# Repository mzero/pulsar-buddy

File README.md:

# Pulsar Buddy

Pulsar Buddy is a small clock unit for the SOMA Lab's Pulsar-23 synth.
It is also useful with other modular synths.

Please see the [Wiki](https://github.com/mzero/pulsar-buddy/wiki) for full
information.

----

Pulsar Buddy is open source hardware and open source software.

The hardware is licensed by CC-SA-3.0. See LICENSE-HW.txt
The software is licensed by BSD3. See LICENSE-SW.txt

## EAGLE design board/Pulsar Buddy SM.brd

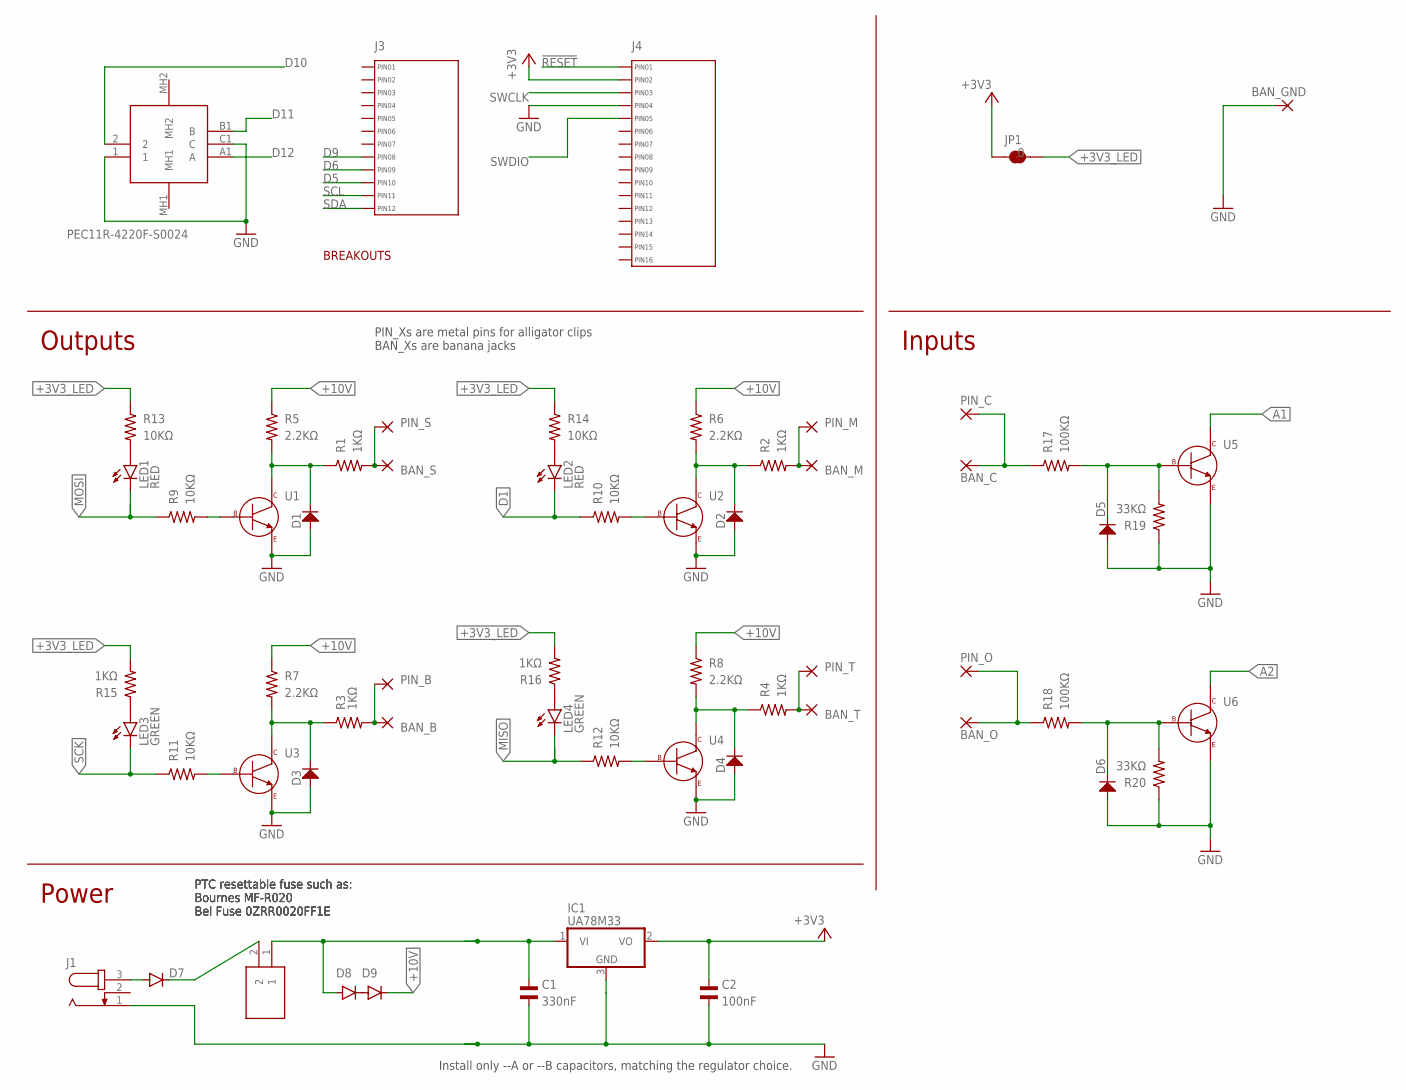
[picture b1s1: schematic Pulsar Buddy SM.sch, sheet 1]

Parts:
BAN_B: WIREPADBANANA; BANANA
BAN_C: WIREPADBANANA; BANANA
BAN_GND: WIREPADBANANA-GND; BANANA-GND
BAN_M: WIREPADBANANA; BANANA
BAN_O: WIREPADBANANA; BANANA
BAN_S: WIREPADBANANA; BANANA
BAN_T: WIREPADBANANA; BANANA
C1: 330nF; C0603; MPN CC0603ZRY5V7BB334
C2: 100nF; C0603; MPN CC0603KRX7R9BB104
D1, D2, D3, D4, D5, D6: MF-DIO-SOD123-BAT42; SOD-123
D7, D8, D9: CGRM4004-G; SOD-123_MINI-SMA; MPN CGRM4004-G
F1: 0ZCJ0020FF2E; FUSC3216X75N; MPN 0ZCJ0020FF2E
IC1: UA78M33; TO252; MPN UA78M33CKVURG3
J1: JACK-PLUG0; SPC4077
J3: MF-CON-2.54mm-01x12; PTH_2.54MM_01X12
J4: MF-CON-2.54mm-01x16; PTH_2.54MM_01X16
JP1: JUMPER-SMT_2_NC_TRACE_SILK; SMT-JUMPER_2_NC_TRACE_SILK
LED1, LED2: RED; LED5MM
LED3, LED4: GREEN; LED5MM
PIN_B: WIREPAD; M3
PIN_C: WIREPAD; M3
PIN_M: WIREPAD; M3
PIN_O: WIREPAD; M3
PIN_S: WIREPAD; M3
PIN_T: WIREPAD; M3
R1, R2, R3, R4, R15, R16: 1KΩ; R0603; MPN MF-RES-0603-1K
R5, R6, R7, R8: 2.2KΩ; R0603; MPN RC0603JR-072K2L
R9, R10, R11, R12, R13, R14: 10KΩ; R0603; MPN MF-RES-0603-10K
R17, R18: 100KΩ; R0603; MPN MF-RES-0603-100K
R19, R20: 33KΩ; R0603; MPN RC0603FR-0733KL
SW1: PEC11R-4220F-S0024; PEC11R4220FS0024; MPN PEC11R-4220F-S0024
U1, U2, U3, U4, U5, U6: MF-DSC-SOT233-MMBT3904; SOT-23-3

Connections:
!RESET: J4.P$1 (PIN1); also elsewhere on the board
+3V3: C2.P$1, IC1.2 (VO), J4.P$2 (PIN2), JP1.1; also elsewhere on the board
+3V3_LED: JP1.2, R13.P$1, R14.P$1, R15.P$2, R16.P$2
+10V: D9.C, R5.P$1, R6.P$1, R7.P$1, R8.P$1
+12V: C1.P$1, D8.A, F1.1, IC1.1 (VI)
A1: U5.P$3 (COLLECTOR); also elsewhere on the board
A2: U6.P$3 (COLLECTOR); also elsewhere on the board
D1: LED2.K (C), R10.P$1; also elsewhere on the board
D5: J3.P$10 (PIN10); also elsewhere on the board
D6: J3.P$9 (PIN9); also elsewhere on the board
D9: J3.P$8 (PIN8); also elsewhere on the board
D10: SW1.2; also elsewhere on the board
D11: SW1.B1 (B); also elsewhere on the board
D12: SW1.A1 (A); also elsewhere on the board
GND: BAN_GND.C, C1.P$2, C2.P$2, D1.ANODE, D2.ANODE, D3.ANODE, D4.ANODE, D5.ANODE, D6.ANODE, IC1.3 (GND), J1.1, J4.P$4 (PIN4), R19.P$1, R20.P$1, SW1.1, SW1.C1 (C), U1.P$2 (EMITTER), U2.P$2 (EMITTER), U3.P$2 (EMITTER), U4.P$2 (EMITTER), U5.P$2 (EMITTER), U6.P$2 (EMITTER); also elsewhere on the board
MISO: LED4.K (C), R12.P$1; also elsewhere on the board
MOSI: LED1.K (C), R9.P$1; also elsewhere on the board
unnamed: R10.P$2, U2.P$1 (BASE)
unnamed: D7.C, F1.2
unnamed: D7.A, J1.3
unnamed: LED1.A, R13.P$2
unnamed: LED2.A, R14.P$2
unnamed: R9.P$2, U1.P$1 (BASE)
unnamed: D1.CATHODE, R1.P$1, R5.P$2, U1.P$3 (COLLECTOR)
unnamed: D2.CATHODE, R2.P$1, R6.P$2, U2.P$3 (COLLECTOR)
unnamed: LED3.A, R15.P$1
unnamed: R11.P$2, U3.P$1 (BASE)
unnamed: D3.CATHODE, R3.P$1, R7.P$2, U3.P$3 (COLLECTOR)
unnamed: LED4.A, R16.P$1
unnamed: R12.P$2, U4.P$1 (BASE)
unnamed: D4.CATHODE, R4.P$1, R8.P$2, U4.P$3 (COLLECTOR)
unnamed: D5.CATHODE, R17.P$2, R19.P$2, U5.P$1 (BASE)
unnamed: BAN_O.C, PIN_O.1, R18.P$1
unnamed: BAN_C.C, PIN_C.1, R17.P$1
unnamed: D6.CATHODE, R18.P$2, R20.P$2, U6.P$1 (BASE)
unnamed: D8.C, D9.A
unnamed: BAN_S.C, PIN_S.1, R1.P$2
unnamed: BAN_M.C, PIN_M.1, R2.P$2
unnamed: BAN_T.C, PIN_T.1, R4.P$2
unnamed: BAN_B.C, PIN_B.1, R3.P$2
SCK: LED3.K (C), R11.P$1; also elsewhere on the board
SCL: J3.P$11 (PIN11); also elsewhere on the board
SDA: J3.P$12 (PIN12); also elsewhere on the board
SWCLK: J4.P$3 (PIN3); also elsewhere on the board
SWDIO: J4.P$5 (PIN5); also elsewhere on the board

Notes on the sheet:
Inputs
Power
Outputs
Install only --A or --B capacitors, matching the regulator choice.
PTC resettable fuse such as: Bournes MF-R020 Bel Fuse 0ZRR0020FF1E
BREAKOUTS
PIN_Xs are metal pins for alligator clips BAN_Xs are banana jacks

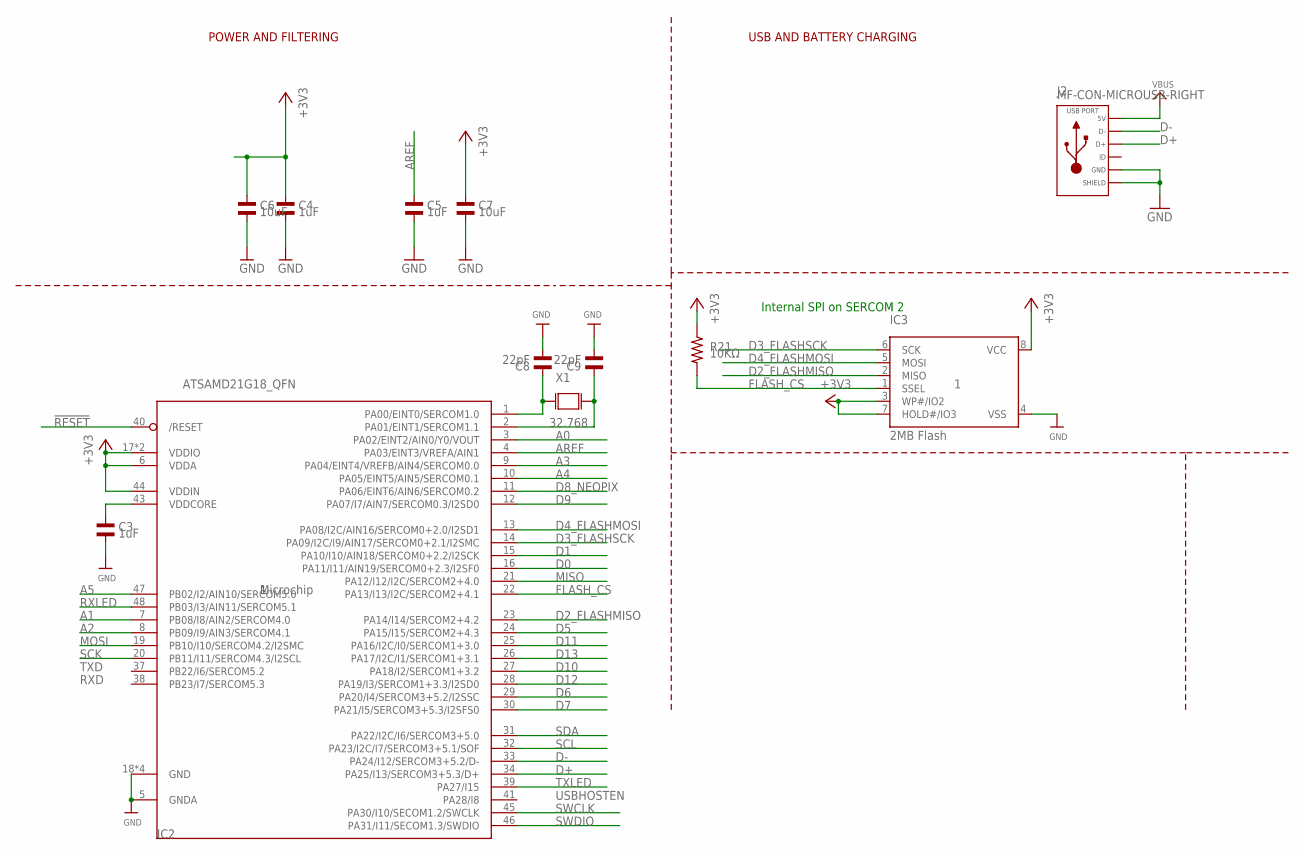
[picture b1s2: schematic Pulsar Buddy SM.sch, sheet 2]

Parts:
C3, C4, C5: 1uF; C0603; MPN MF-CAP-0603-1uF
C6, C7: 10uF; C0603; MPN 0603ZD106KAT2A
C8, C9: 22pF; C0603; MPN MF-CAP-0603-22pF
IC2: ATSAMD21G18_QFN; TQFN48_7MM; MPN SAMD21G18A-MU
IC3: 2MB Flash; SOIC8_208MIL; MPN S25FL064LABMFI010
J2: MF-CON-MICROUSB-RIGHT; MICROUSB-RIGHT
R21: 10KΩ; R0603; MPN MF-RES-0603-10K
U$34, U$35: FIDUCIAL_100MIL
X1: 32.768; ECX-31B_SERIES; MPN ECS-.327-7-12-C-TR

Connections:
!RESET: IC2.40 (/RESET); also elsewhere on the board
+3V3: C4.P$1, C6.P$1, C7.P$1, IC2.6 (VDDA), IC2.17 (VDDIO), IC2.36 (VDDIO), IC2.44 (VDDIN), IC3.3 (WP#/IO2), IC3.7 (HOLD#/IO3), IC3.8 (VCC), R21.P$1; also elsewhere on the board
A0: IC2.3 (PA02/EINT2/AIN0/Y0/VOUT)
A1: IC2.7 (PB08/I8/AIN2/SERCOM4.0); also elsewhere on the board
A2: IC2.8 (PB09/I9/AIN3/SERCOM4.1); also elsewhere on the board
A3: IC2.9 (PA04/EINT4/VREFB/AIN4/SERCOM0.0)
A4: IC2.10 (PA05/EINT5/AIN5/SERCOM0.1)
A5: IC2.47 (PB02/I2/AIN10/SERCOM5.0)
AREF: C5.P$1, IC2.4 (PA03/EINT3/VREFA/AIN1)
D0: IC2.16 (PA11/I11/AIN19/SERCOM0+2.3/I2SF0)
D1: IC2.15 (PA10/I10/AIN18/SERCOM0+2.2/I2SCK); also elsewhere on the board
D2_FLASHMISO: IC2.23 (PA14/I14/SERCOM2+4.2), IC3.2 (MISO)
D3_FLASHSCK: IC2.14 (PA09/I2C/I9/AIN17/SERCOM0+2.1/I2SMC), IC3.6 (SCK)
D4_FLASHMOSI: IC2.13 (PA08/I2C/AIN16/SERCOM0+2.0/I2SD1), IC3.5 (MOSI)
D5: IC2.24 (PA15/I15/SERCOM2+4.3); also elsewhere on the board
D6: IC2.29 (PA20/I4/SERCOM3+5.2/I2SSC); also elsewhere on the board
D7: IC2.30 (PA21/I5/SERCOM3+5.3/I2SFS0)
D8_NEOPIX: IC2.11 (PA06/EINT6/AIN6/SERCOM0.2)
D9: IC2.12 (PA07/I7/AIN7/SERCOM0.3/I2SD0); also elsewhere on the board
D10: IC2.27 (PA18/I2/SERCOM1+3.2); also elsewhere on the board
D11: IC2.25 (PA16/I2C/I0/SERCOM1+3.0); also elsewhere on the board
D12: IC2.28 (PA19/I3/SERCOM1+3.3/I2SD0); also elsewhere on the board
D13: IC2.26 (PA17/I2C/I1/SERCOM1+3.1)
D+: IC2.34 (PA25/I13/SERCOM3+5.3/D+), J2.3 (D+)
D-: IC2.33 (PA24/I12/SERCOM3+5.2/D-), J2.2 (D-)
FLASH_CS: IC2.22 (PA13/I13/I2C/SERCOM2+4.1), IC3.1 (SSEL), R21.P$2
GND: C3.P$2, C4.P$2, C5.P$2, C6.P$2, C7.P$2, C8.P$2, C9.P$2, IC2.5 (GNDA), IC2.18 (GND), IC2.35 (GND), IC2.42 (GND), IC2.THERMAL (GND), IC3.4 (VSS), J2.5 (GND), J2.S1 (SLD), J2.S2 (SLD), J2.S3 (SLD), J2.S4 (SLD), J2.S5 (SLD), J2.S6 (SLD); also elsewhere on the board
MISO: IC2.21 (PA12/I12/I2C/SERCOM2+4.0); also elsewhere on the board
MOSI: IC2.19 (PB10/I10/SERCOM4.2/I2SMC); also elsewhere on the board
unnamed: C8.P$1, IC2.1 (PA00/EINT0/SERCOM1.0), X1.P$1 (X0)
unnamed: C9.P$1, IC2.2 (PA01/EINT1/SERCOM1.1), X1.P$2 (X1)
RXLED: IC2.48 (PB03/I3/AIN11/SERCOM5.1)
SCK: IC2.20 (PB11/I11/SERCOM4.3/I2SCL); also elsewhere on the board
SCL: IC2.32 (PA23/I2C/I7/SERCOM3+5.1/SOF); also elsewhere on the board
SDA: IC2.31 (PA22/I2C/I6/SERCOM3+5.0); also elsewhere on the board
SWCLK: IC2.45 (PA30/I10/SECOM1.2/SWCLK); also elsewhere on the board
SWDIO: IC2.46 (PA31/I11/SECOM1.3/SWDIO); also elsewhere on the board
TXLED: IC2.39 (PA27/I15)
VBUS: J2.1 (5V)
VDDCORE1: C3.P$1, IC2.43 (VDDCORE)

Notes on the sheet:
POWER AND FILTERING
USBHOSTEN
TXD
RXD
USB AND BATTERY CHARGING
Internal SPI on SERCOM 2

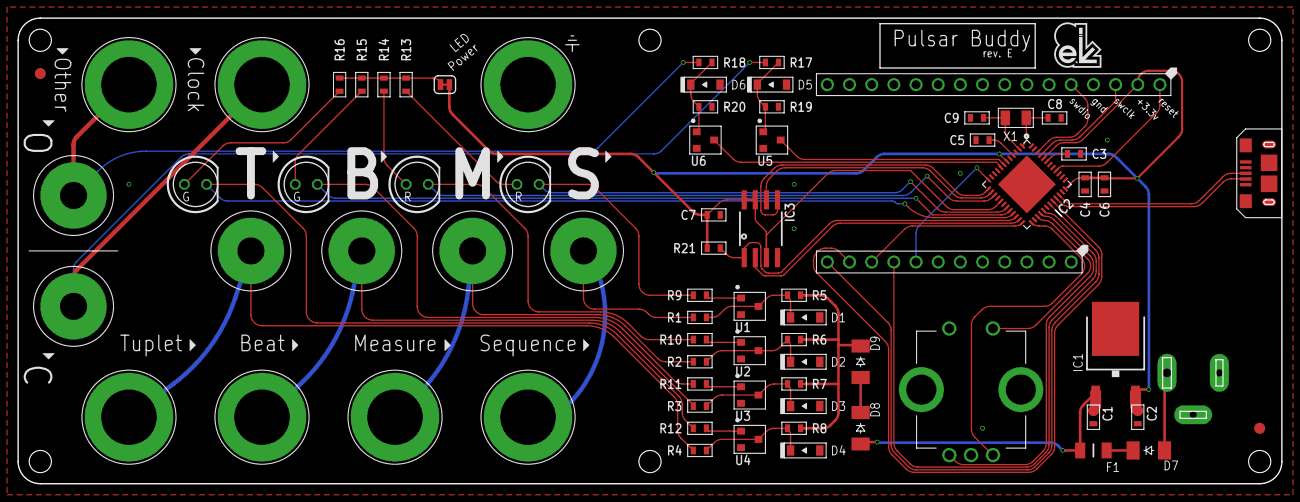
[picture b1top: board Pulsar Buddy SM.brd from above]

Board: 2 copper layers, 144.8 x 53.3 mm, 75 parts (1 on the bottom side), 55 nets.

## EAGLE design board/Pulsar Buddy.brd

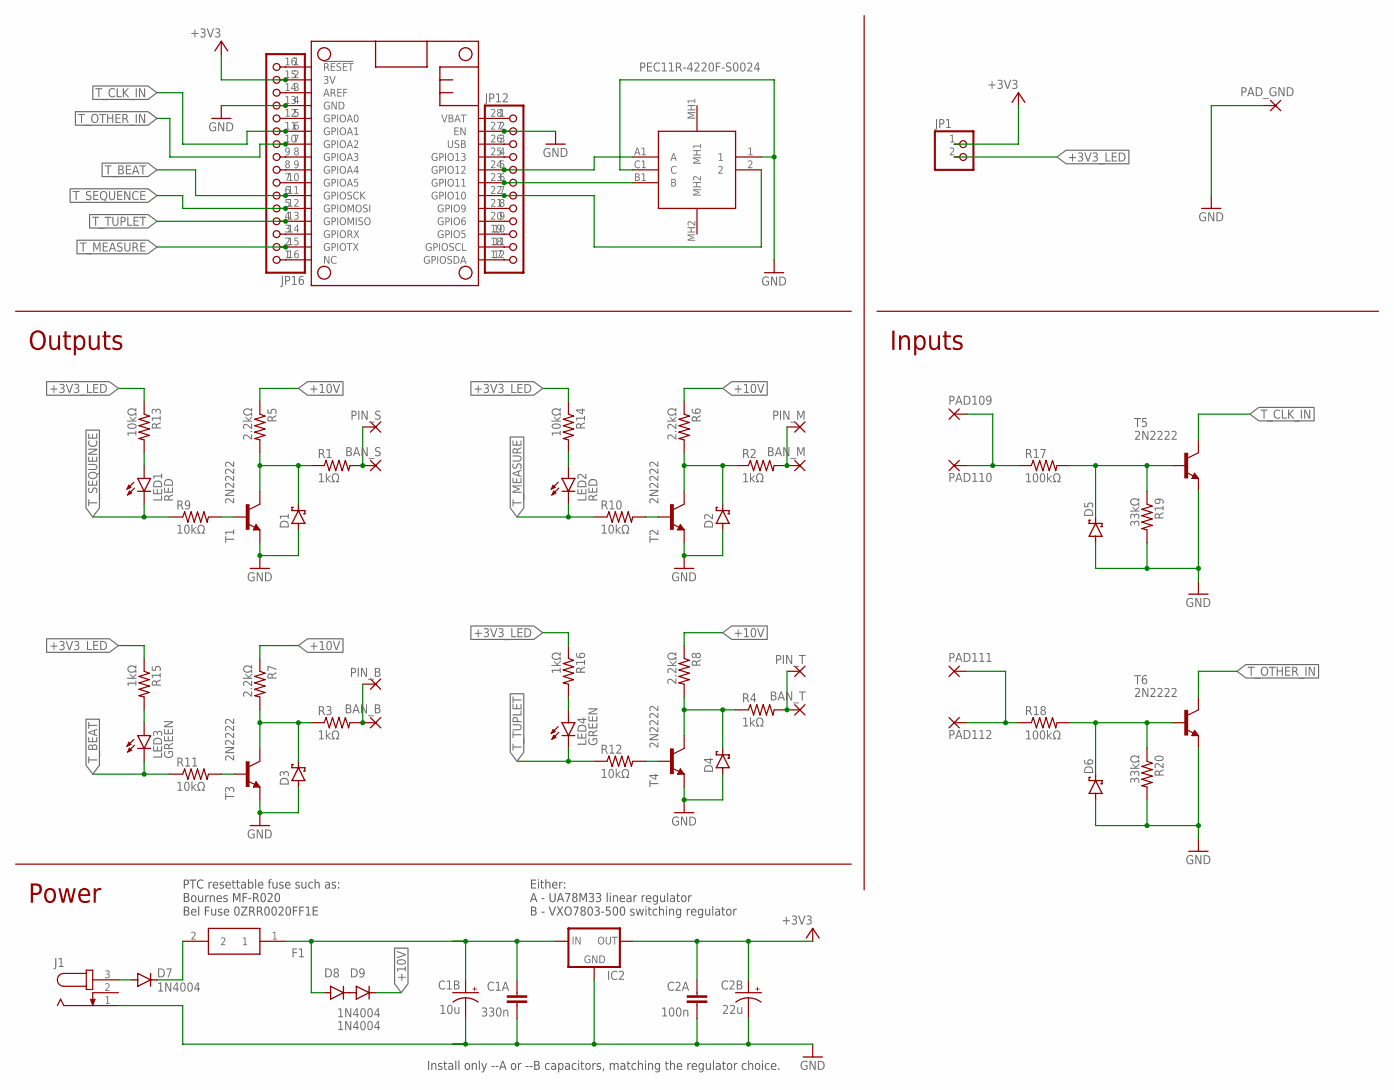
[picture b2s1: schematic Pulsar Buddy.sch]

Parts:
BAN_B: WIREPADBANANA; BANANA
BAN_M: WIREPADBANANA; BANANA
BAN_S: WIREPADBANANA; BANANA
BAN_T: WIREPADBANANA; BANANA
C1A: 330n; C025-024X044
C1B: 10u; E5-5
C2A: 100n; C025-024X044
C2B: 22u; E5-5
D1, D2, D3, D4, D5, D6: SCHOTTKY-DIODEDO35-7; DO35-7
D7, D8, D9: 1N4004; DO41-10
F1: 0ZRR0025FF1E
IC2: UA78M33CKCSTO-220; TO220H
J1: JACK-PLUG0; SPC4077
JP1: PINHD-1X2; 1X02
JP12: HEADER-1X12; 1X12_ROUND
JP16: HEADER-1X16ROUND; 1X16_ROUND
LED1, LED2: RED; LED5MM
LED3, LED4: GREEN; LED5MM
MS101: FEATHERWING_NODIM; FEATHERWING_DIM
PAD109, PAD111: WIREPAD; M3
PAD110, PAD112: WIREPADBANANA; BANANA
PAD_GND: WIREPADBANANA-GND; BANANA-GND
PIN_B: WIREPAD; M3
PIN_M: WIREPAD; M3
PIN_S: WIREPAD; M3
PIN_T: WIREPAD; M3
R1, R2, R3, R4, R15, R16: 1kΩ; 0204/7
R5, R6, R7, R8: 2.2kΩ; 0204/7
R9, R10, R11, R12, R13, R14: 10kΩ; 0204/7
R17, R18: 100kΩ; 0204/7
R19, R20: 33kΩ; 0204/7
SW1: PEC11R-4220F-S0024; PEC11R4220FS0024
T1, T2, T3, T4, T5, T6: 2N2222; TO92-EBC-OVAL

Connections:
+3V3: C2A.1, C2B.+, IC2.3 (OUT), JP1.1, JP16.15, MS101.2 (3V)
+3V3_LED: JP1.2, R13.1, R14.1, R15.1, R16.1
+5V_CPU: JP12.3, MS101.26 (USB)
+10V: D9.C, R5.1, R6.1, R7.1, R8.1
+12V: C1A.1, C1B.+, D8.A, F1.1, IC2.1 (IN)
GND: C1A.2, C1B.-, C2A.2, C2B.-, D1.A, D2.A, D3.A, D4.A, D5.A, D6.A, IC2.2 (GND), J1.1, JP12.2, JP16.13, MS101.4 (GND), MS101.27 (EN), PAD_GND.C, R19.2, R20.2, SW1.1, SW1.C1 (C), T1.E, T2.E, T3.E, T4.E, T5.E, T6.E
unnamed: JP12.5, MS101.24 (GPIO12), SW1.A1 (A)
unnamed: JP12.7, MS101.22 (GPIO10), SW1.2
unnamed: JP12.6, MS101.23 (GPIO11), SW1.B1 (B)
unnamed: D7.C, F1.2
unnamed: D7.A, J1.3
unnamed: LED1.A, R13.2
unnamed: LED2.A, R14.2
unnamed: R9.2, T1.B
unnamed: D1.C, R1.1, R5.2, T1.C
unnamed: R10.2, T2.B
unnamed: D2.C, R2.1, R6.2, T2.C
unnamed: LED3.A, R15.2
unnamed: R11.2, T3.B
unnamed: D3.C, R3.1, R7.2, T3.C
unnamed: LED4.A, R16.2
unnamed: R12.2, T4.B
unnamed: D4.C, R4.1, R8.2, T4.C
unnamed: D5.C, R17.2, R19.1, T5.B
unnamed: PAD111.1, PAD112.C, R18.1
unnamed: PAD109.1, PAD110.C, R17.1
unnamed: D6.C, R18.2, R20.1, T6.B
unnamed: JP16.16, MS101.1 (!RESET)
unnamed: JP16.14, MS101.3 (AREF)
unnamed: JP16.12, MS101.5 (GPIOA0)
unnamed: JP16.9, MS101.8 (GPIOA3)
unnamed: JP16.8, MS101.9 (GPIOA4)
unnamed: JP16.7, MS101.10 (GPIOA5)
unnamed: JP16.3, MS101.14 (GPIORX)
unnamed: JP16.1, MS101.16 (NC)
unnamed: JP12.12, MS101.17 (GPIOSDA)
unnamed: JP12.11, MS101.18 (GPIOSCL)
unnamed: JP12.10, MS101.19 (GPIO5)
unnamed: JP12.8, MS101.21 (GPIO9)
unnamed: JP12.9, MS101.20 (GPIO6)
unnamed: JP12.4, MS101.25 (GPIO13)
unnamed: D8.C, D9.A
unnamed: BAN_S.C, PIN_S.1, R1.2
unnamed: BAN_M.C, PIN_M.1, R2.2
unnamed: BAN_T.C, PIN_T.1, R4.2
unnamed: BAN_B.C, PIN_B.1, R3.2
T_BEAT: JP16.6, LED3.K (C), MS101.11 (GPIOSCK), R11.1
T_CLK_IN: JP16.11, MS101.6 (GPIOA1), T5.C
T_MEASURE: JP16.2, LED2.K (C), MS101.15 (GPIOTX), R10.1
T_OTHER_IN: JP16.10, MS101.7 (GPIOA2), T6.C
T_SEQUENCE: JP16.5, LED1.K (C), MS101.12 (GPIOMOSI), R9.1
T_TUPLET: JP16.4, LED4.K (C), MS101.13 (GPIOMISO), R12.1
VBAT: JP12.1, MS101.28 (VBAT)

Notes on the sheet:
Inputs
Power
Outputs
Either: A - UA78M33 linear regulator B - VXO7803-500 switching regulator
Install only --A or --B capacitors, matching the regulator choice.
PTC resettable fuse such as: Bournes MF-R020 Bel Fuse 0ZRR0020FF1E

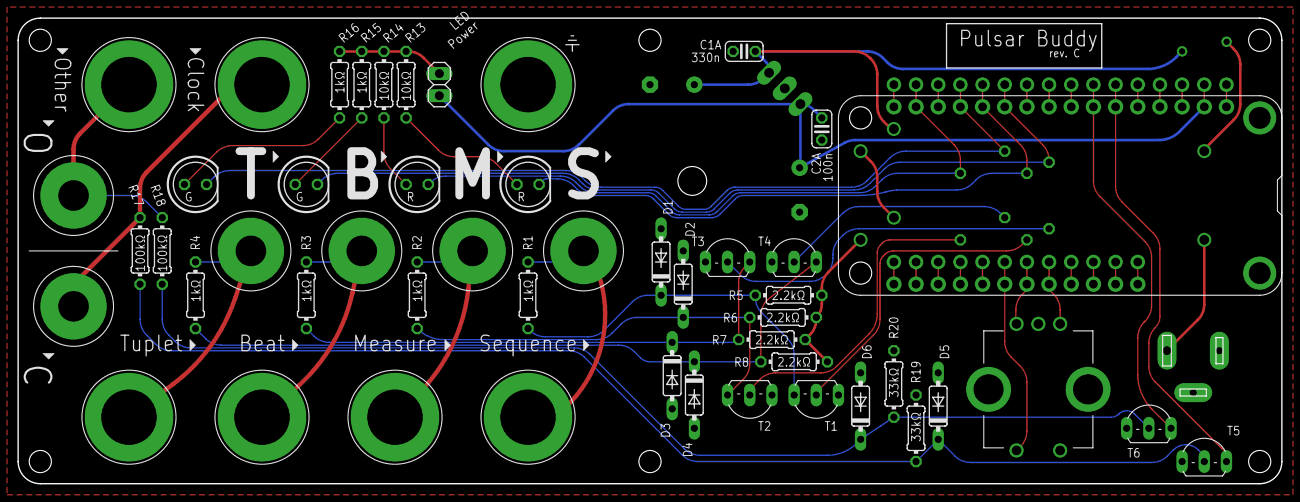
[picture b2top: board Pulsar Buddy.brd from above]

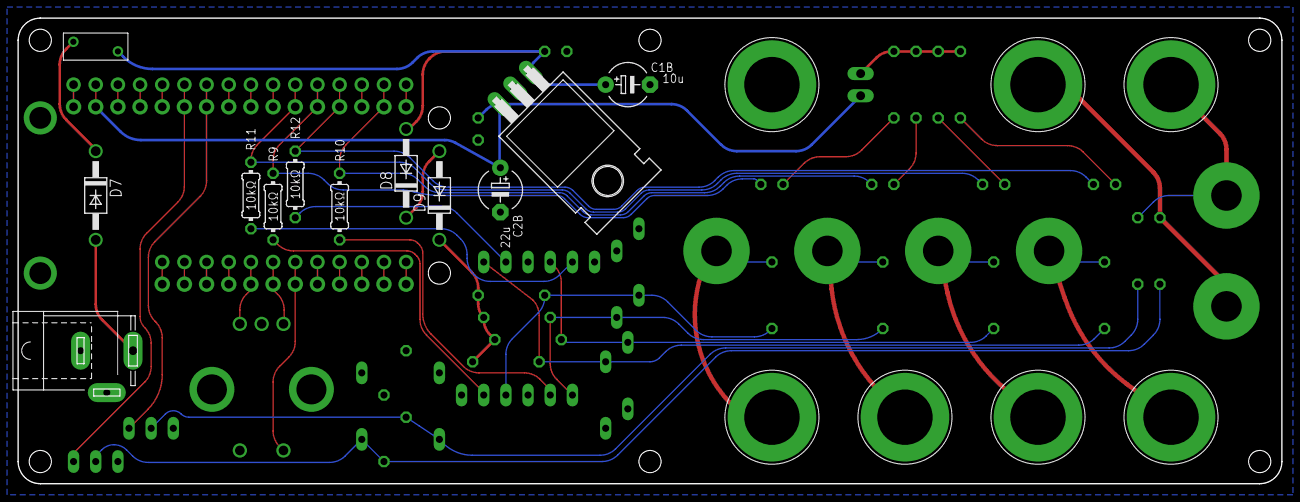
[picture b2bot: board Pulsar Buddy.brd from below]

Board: 2 copper layers, 144.8 x 53.3 mm, 64 parts (12 on the bottom side), 53 nets.

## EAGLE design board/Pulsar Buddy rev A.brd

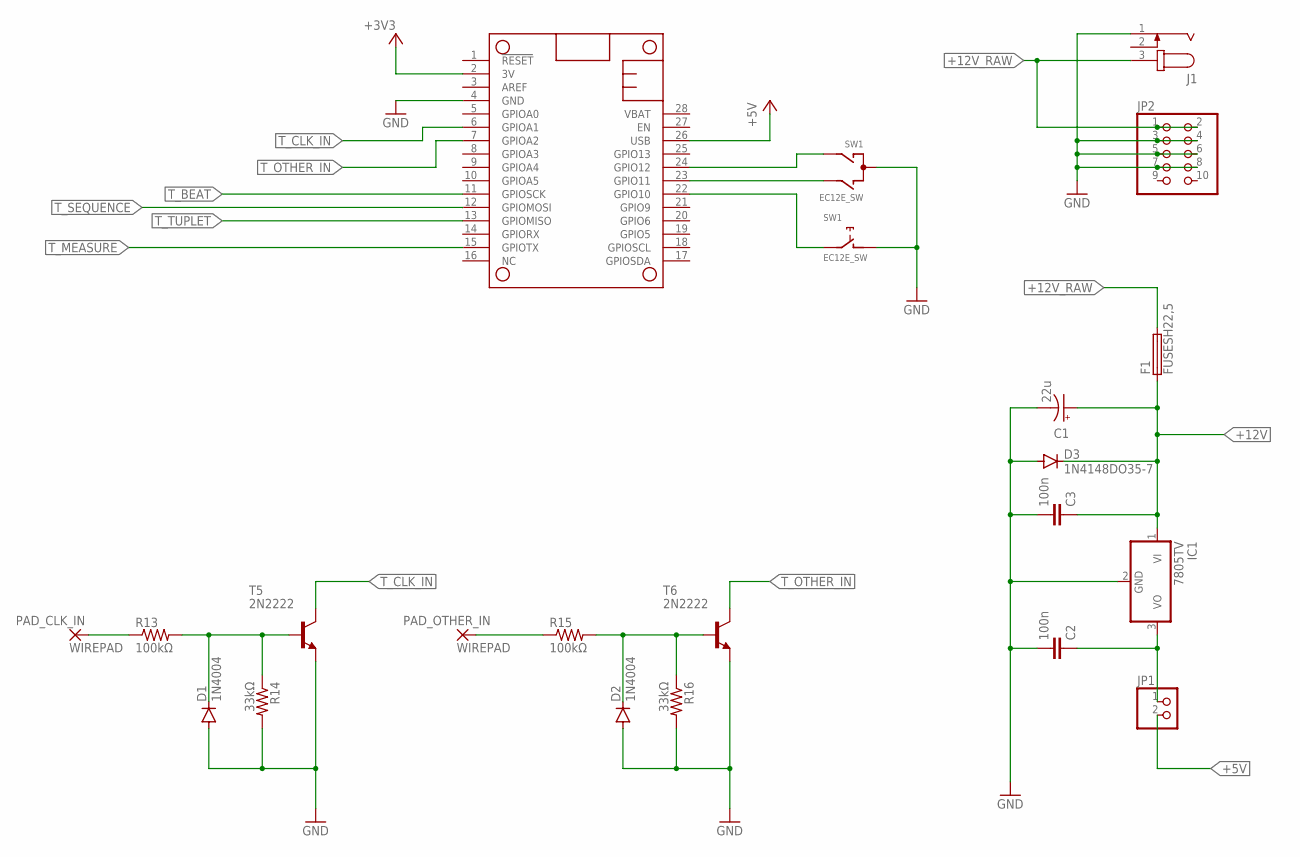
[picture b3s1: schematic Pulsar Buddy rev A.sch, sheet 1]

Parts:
C1: 22u; E3,5-8
C2, C3: 100n; C025-024X044
D1, D2: 1N4004; DO41-10
D3: 1N4148DO35-7; DO35-7
F1: FUSESH22,5; SH22,5
IC1: 7805TV; TO220V
J1: JACK-PLUG0; SPC4077
JP1: PINHD-1X2; 1X02
JP2: PINHD-2X5; 2X05
MS2: FEATHERWING_NODIM; FEATHERWING_DIM
PAD_CLK_IN: WIREPAD; M3
PAD_OTHER_IN: WIREPAD; M3
R13, R15: 100kΩ; 0204/7
R14, R16: 33kΩ; 0204/7
SW1: EC12E_SW; ALPS_EC12E_SW
T5, T6: 2N2222; TO92-EBC-OVAL

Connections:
+3V3: MS2.2 (3V); also elsewhere on the board
+5V: JP1.2, MS2.26 (USB); also elsewhere on the board
+12V: C1.+, C3.1, D3.C, F1.1, IC1.1 (VI); also elsewhere on the board
+12V_RAW: F1.2, J1.3, JP2.1, JP2.2
GND: C1.-, C2.2, C3.2, D1.A, D2.A, D3.A, IC1.2 (GND), J1.1, JP2.3, JP2.4, JP2.5, JP2.6, JP2.7, JP2.8, MS2.4 (GND), R14.2, R16.2, SW1.C, SW1.D (1), T5.E, T6.E; also elsewhere on the board
unnamed: MS2.24 (GPIO12), SW1.A
unnamed: MS2.22 (GPIO10), SW1.E (2)
unnamed: MS2.23 (GPIO11), SW1.B
unnamed: C2.1, IC1.3 (VO), JP1.1
unnamed: D1.C, R13.2, R14.1, T5.B
unnamed: PAD_OTHER_IN.1, R15.1
unnamed: PAD_CLK_IN.1, R13.1
unnamed: D2.C, R15.2, R16.1, T6.B
T_BEAT: MS2.11 (GPIOSCK); also elsewhere on the board
T_CLK_IN: MS2.6 (GPIOA1), T5.C
T_MEASURE: MS2.15 (GPIOTX); also elsewhere on the board
T_OTHER_IN: MS2.7 (GPIOA2), T6.C
T_SEQUENCE: MS2.12 (GPIOMOSI); also elsewhere on the board
T_TUPLET: MS2.13 (GPIOMISO); also elsewhere on the board

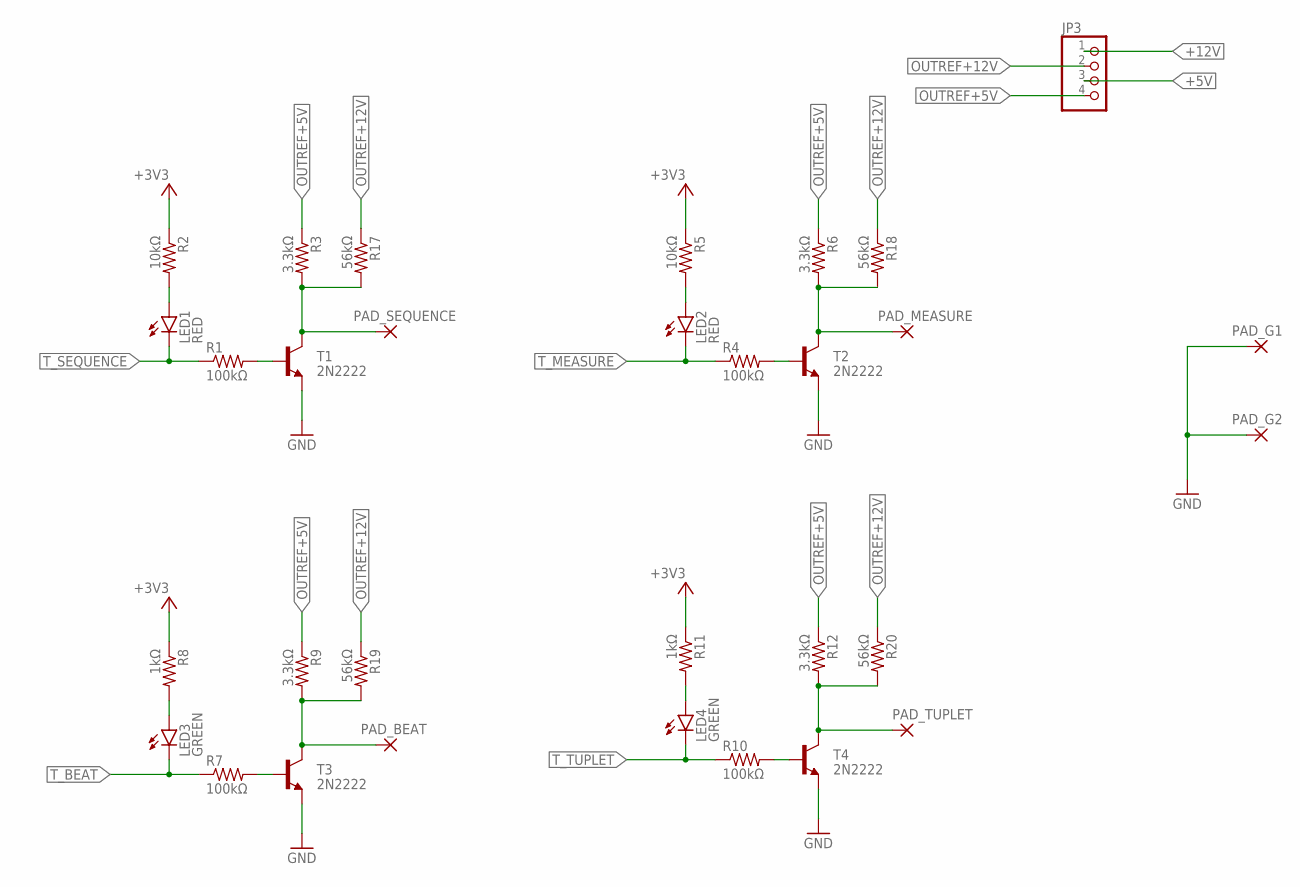
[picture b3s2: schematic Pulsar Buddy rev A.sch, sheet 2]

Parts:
JP3: PINHD-1X4; 1X04
LED1, LED2: RED; LED5MM
LED3, LED4: GREEN; LED5MM
PAD_BEAT: WIREPAD; M3
PAD_G1, PAD_G2: WIREPAD; M3
PAD_MEASURE: WIREPAD; M3
PAD_SEQUENCE: WIREPAD; M3
PAD_TUPLET: WIREPAD; M3
R1, R4, R7, R10: 100kΩ; 0204/7
R2, R5: 10kΩ; 0204/7
R3, R6, R9, R12: 3.3kΩ; 0204/7
R8, R11: 1kΩ; 0204/7
R17, R18, R19, R20: 56kΩ; 0204/7
T1, T2, T3, T4: 2N2222; TO92-EBC-OVAL

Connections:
+3V3: R2.1, R5.1, R8.1, R11.1; also elsewhere on the board
+5V: JP3.3; also elsewhere on the board
+12V: JP3.1; also elsewhere on the board
GND: PAD_G1.1, PAD_G2.1, T1.E, T2.E, T3.E, T4.E; also elsewhere on the board
unnamed: LED1.A, R2.2
unnamed: LED2.A, R5.2
unnamed: R1.2, T1.B
unnamed: PAD_SEQUENCE.1, R3.2, R17.2, T1.C
unnamed: R4.2, T2.B
unnamed: PAD_MEASURE.1, R6.2, R18.2, T2.C
unnamed: LED3.A, R8.2
unnamed: R7.2, T3.B
unnamed: PAD_BEAT.1, R9.2, R19.2, T3.C
unnamed: LED4.A, R11.2
unnamed: R10.2, T4.B
unnamed: PAD_TUPLET.1, R12.2, R20.2, T4.C
OUTREF+5V: JP3.4, R3.1, R6.1, R9.1, R12.1
OUTREF+12V: JP3.2, R17.1, R18.1, R19.1, R20.1
T_BEAT: LED3.K (C), R7.1; also elsewhere on the board
T_MEASURE: LED2.K (C), R4.1; also elsewhere on the board
T_SEQUENCE: LED1.K (C), R1.1; also elsewhere on the board
T_TUPLET: LED4.K (C), R10.1; also elsewhere on the board

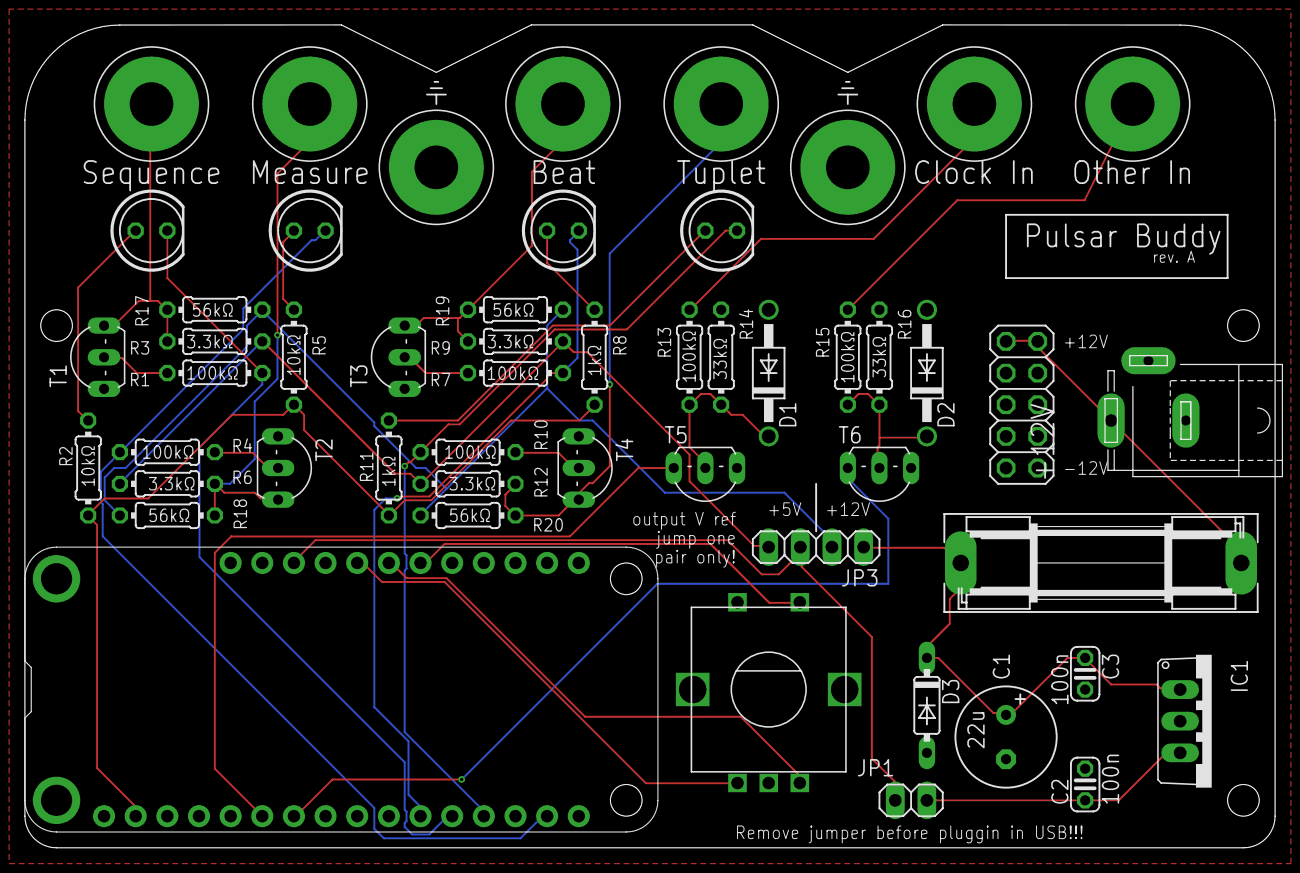
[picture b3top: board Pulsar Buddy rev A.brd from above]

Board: 2 copper layers, 100.3 x 66.0 mm, 52 parts (0 on the bottom side), 33 nets.

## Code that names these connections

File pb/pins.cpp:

#include "pins.h"

#include <Arduino.h>
#include <wiring_private.h>

/*
  Output pins are:
                timer   wave    samd pin    arduino pin
    SEQUENCE:   TCC0    WO4     PB10        29, PIN_SPI_MOSI
    MEASURE:    TCC1    WO0     PA10         1, PIN_SERIAL1_TX
    BEAT:       TC5     WO1     PB11        30, PIN_SPI_SCK
    TUPLET:     TCC2    WO0     PA12        28, PIN_SPI_MISO

    Despite the Adafruit's pinout diagram, these are the actual library pin
    numbers for the SPI pins on the Feather M0 Express.

  Input pins:
    EXT CLK:                    PB08        15, PIN_A1
    OTHER:                      PB09        16, PIN_A2


  NB: If you want to change the pin assignments, then you must carefully
  review and adjust the timer assignments in timer_hw.cpp so that each
  timer has an output waveform that can be assigned to the pin you want to
  use.

*/

TriggerOutput TriggerOutput::S(PIN_SPI_MOSI);
TriggerOutput TriggerOutput::M(PIN_SERIAL1_TX);
TriggerOutput TriggerOutput::B(PIN_SPI_SCK);
TriggerOutput TriggerOutput::T(PIN_SPI_MISO);

TriggerInput TriggerInput::C(PIN_A1);
TriggerInput TriggerInput::O(PIN_A2);


// NORMAL OPERATION

void TriggerOutput::initialize() {
  // Pins are configured as outputs, first, set to HIGH...
  // ...then configured to output the from the peripheral multiplexor.
  // This way, all triggers can be forced off (HIGH, they invert), by just
  // disabling the multiplexor for them.

  digitalWrite(pin, HIGH);
  pinPeripheral(pin, pin == PIN_SPI_MOSI ? PIO_TIMER_ALT : PIO_TIMER);
}

void TriggerOutput::disable(bool off) {
  PORT->Group[g_APinDescription[pin].ulPort]
    .PINCFG[g_APinDescription[pin].ulPin]
      .bit.PMUXEN = off ? 0 : 1;
}

void TriggerInput::initialize() {
  pinMode(pin, INPUT_PULLUP);
  pinPeripheral(pin, PIO_EXTINT);
}

bool TriggerInput::read() {
  return digitalRead(pin) == LOW;     // inputs are inverted
}


// TEST MODE OPERATION

void TriggerOutput::testInitialize() {
  pinMode(pin, OUTPUT);
  pinPeripheral(pin, PIO_OUTPUT);
}

void TriggerOutput::testWrite(bool on) {
  digitalWrite(pin, on ? LOW : HIGH);   // outputs are inverted
}


void TriggerInput::testInitialize() {
  pinMode(pin, INPUT_PULLUP);
  pinPeripheral(pin, PIO_INPUT_PULLUP);
}

bool TriggerInput::testRead() {
  return digitalRead(pin) == LOW;     // inputs are inverted
}

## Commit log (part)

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2019-11-23 first sketch w/working UI
2019-11-23 work on display routines
2019-11-24 Field and ValueField templates & selection menus
2019-11-24 dim timer
    - and some Serial debugging cleanups
2019-11-24 sublime project
2019-11-24 include separators in compound option fields
2019-11-25 make list of fields be a std::initializer_list
2019-11-25 some small C++ cleanups
2019-11-26 quantum and beat timers!!
2019-11-26 breaking out timing.h/.cpp
2019-11-27 make beat output be the beat from the tuplet
2019-11-27 remove unneeded pinMode() calls
2019-11-30 circuit and layout files
2019-11-30 update to TODO
2019-11-30 simplify memory display
2019-11-30 plumb interrupt to main loop on each measure
2019-11-30 state improvements
    - Settings and State classes
    - user and active Settings
    - commit to active settings on measure events
2019-12-01 button states
2019-12-01 plumb encoder button state to Filed::click() in case the selected field wants it
2019-12-01 complete memory UI
    - selection and update updates a temporary selection
    - click loads selection
    - long press saves into selected memory - with UI feedback
2019-12-01 added enter() and exit() functions for Fields
2019-12-01 support for preview state
2019-12-02 first flash storage
2019-12-03 flash improvements: new hash, and speed up bitmap scan loop
2019-12-03 restructured Flash API: Persistent is no more, long live FlashLog
2019-12-03 commit to using our own fork of Adafruit_SPIFlash
    - code uses our Adafruit_SPIFlashCore, which saves 4k of SRAM!
2019-12-03 switch to 8bit values for Settings fields
2019-12-03 persist and restore the active State
2019-12-04 updated circuit
2019-12-04 expanded State with SyncMode, and added SyncField
2019-12-05 improve sync mode display
2019-12-05 capture sync clk in
2019-12-06 rationalize API of BPM and Divisors
    - and tracking BPM now sort of works... if slow
2019-12-06 averaging a beat's worth of divisor calculations
2019-12-06 cleaned up loop(), saving State, and initializingTimers
2019-12-09 invert outputs as new buffer needs them inverted
2019-12-11 update for new version of split Adafruit_SPIFlash classes
2019-12-11 improve sync. safety and code clarity of capture() variables
2019-12-11 delay committing sync mode until field exit
2019-12-12 timing debugging dump routines
2019-12-12 fix drift issue
2019-12-13 ext clk is seen inverted due to input buffer
2019-12-13 improve ext clock rate filtering
    - filter over two beats worth of samples
    - separate out target BPM (measured from ext clock, and shown to user)...
    - ...from actual divisor (includes phase correction)
2019-12-13 clean up compiler warnings
2019-12-13 rounding properly in capture()
2019-12-14 be very rigorous about numeric conversions in timing_hw.cpp code
2019-12-14 tweaked BPM responsiveness
2019-12-15 images for sync modes - and drop tap tempo mode
2019-12-16 ensure BPM is udpated the first time it is asked for
2019-12-16 memory usage on Serial at start-up
    - will eventually have to make this be only in debug builds
2019-12-16 Encoder acceleration (and new Encoder::Update type)
2019-12-17 ClockStatus, and support for detecting and displaying Perplexed state
2019-12-17 basic watchdog timer to detect stopped clock
2019-12-19 longer watchdog while perplexed
2019-12-20 easier way to enable/disable ZeroRegs
2019-12-20 when starting, besure initial triggers all fire
2019-12-21 screen saver!!!
2019-12-22 force triggers off when not running
2019-12-23 tickle timeouts at start
2019-12-23 move controls into controls.h/.cpp
2019-12-23 hook up configuration.screen flags
2019-12-24 fixup
2019-12-24 initialize display in display.cpp
2019-12-24 make flash.cpp faults use new critical error reporting
    - also fix main .ino so that it can display early critical messages
2019-12-24 make timing.cpp use critical
2020-01-14 update TODOs
2020-01-14 box design
2020-01-15 update box
    - support SVG output
    - support calling it from the command line
2020-01-16 update box pcb with split feathers and power connector
2020-01-17 add version.h
2020-01-17 rejigger and rename configuration options
    - also add extendedBpmRange option
2020-01-17 raise lower feather to allow space for USB jack
2020-01-17 improve long press behavior
    - shortened the time for long press
    - made it work even if the field is already selected for value editing
2020-01-19 add schematic pdf
2020-02-05 updated dimensions
    - height of pulsar
    - spacing of lower feather
    - box dimension calculation (make it "always hit the top")
    - adjust the arc location
2020-02-05 redesign
    - added standoffs to pcb object
    - cut out just pins and knob from box top
    - show inner box standing on foot standoffs
2020-02-18 redo case in light of new Pulsar-23 measurements.
2020-02-19 images for WIKI pages
2020-02-22 box changes
    - pins are 16mm
    - screw heads modeled more accurately
    - bottom standoffs replaced with screw heads
    - when nested, move inner box up into outer box more
2020-02-22 make box flat layout be compact
    - includes several fudge factors!
2020-02-22 revision C boxes
2020-03-03 Rev C2 boxes
    - center tabs now fill out (as arc intersected them)
    - location of hole for knob fixed
    - box gap increased to 0.75mm per edge
    - power socket access
    - hole for knob shaft in acrylic plate
2020-03-09 console.log plate dimensions
2020-03-28 support for screenshot to PBM format over Serial line
2020-04-09 beginnings of a test mode
2020-04-09 test mode patterns
2020-04-10 factored out pin code into new pins.h and pins.cpp
2020-04-10 v104 release
2020-05-18 update picture for wiki to a better one
2020-05-20 First version of boxes for SMT version
2020-05-20 updated side with connectors to have vents
    - looks cool, even if the SMT board doesn't need venting!
2020-06-03 surface mount Box and plate
2020-06-04 rev. E board (SMT)
    - smaller holes for screw posts
    - minor aesthetic trace layout changes
2020-06-04 adjusted image location
2020-06-06 v105 release
2020-06-25 abstract out the versioned Container pattern
2020-06-26 low level support for pulse width options
2020-06-27 Add Frame ui class
2020-06-27 Split BPM and Sync fields, and move to two different layouts as main screen
2020-06-28 Return button class to return to main screen
2020-06-28 use ReturnField rather than long-press to get back to main screen
2020-06-28 add static display to pins on setup page
2020-06-28 use the user set pulse widths to set the actual pulse widths
    since pulseWidthX is in State, needed to change some code to pass around references to State, not Settings
    added checks for changes to pulse widths to pendingState() check
2020-06-29 re-work types in timing.h to support upcoming changes
    - decoupled the four pin periods & widths from the logical settings of sequence and measure length
    - split out Offsets as its own type
    - 'nextMeasure' field is for upcoming measure compare register on the sequence timer.
2020-06-30 remove nextMeasure in Offsets structure - it was a bad idea!
2020-06-30 use buffered CC for widths when possible
    - this avoids occasionally very long pulses when the user changes width to very small while it is high
    - not so worrisome for B, which uses a TC that has no buffering for CC - because that must always be a shorter period
2020-06-30 commit to new measure tracking scheme
2020-07-11 add a flash erase and test function to configuration screen
2020-07-11 fix issues with UI state and long presses
2020-07-13 rename _containerLog to just _log in Container class
2020-07-13 rework the initialize() and upgrade() helper function signatures
    - moved out of Container class, to make specialization easier
    - also introduce typedef for State_v2
2020-07-14 v106 release
2020-09-27 fix missing return
2020-09-27 add midi subsystem
    and add basic Midi Clock output
2020-09-29 clean up definition of SyncMode data type
2020-09-30 setOffsets() in timing module
2020-10-06 improved ISR state debugging
2020-10-09 small fixes to clock ISR
2020-10-09 add dAdj to clock debugging
2020-10-09 implement full MIDI clock suite
2020-10-11 move clock debug code out of the way into a .hpp file
2020-10-11 remove some unused variables
2020-10-13 massive re-write of clock ISRs
    - unify much of the code so it isn't in a giant switch(clockState)
    - always update sequenceSample if adjusting currentPosition at start of isrClock
    - allow divisors that are very far out of range.... meld them into the capture buffer,
    - they will get evened out
    - handles the crazy timing at the start from non-1/16 note boundaries in Live
    - simplify the phase adjust code
2020-10-22 handle external clocks when explicitly stopped
    - like MIDI devices that send clock when stopped
    - leave quantum running all the time - so that tempo estimation can continue
    - save and restore counts around periods of pause or stopped
2020-10-23 clean up MIDI start and name USB connection
2020-10-24 fix bug in Sync mode display
    - wasn't displaying correctly the first time
    - improved logic
2020-10-24 Fix bug in Sync display
2020-10-26 improve ext clk pause response
    - notice pause after only a 1/16th note (or 2 ext clks, whichever is bigger)
    - after pause, resume count one ext. clk after last
    This generally means backing up... since the clock will have carried on a bit
    after the last ext clk, before the pause was noticed.
2020-10-26 drop watchdog sample from isrClockCapture
2020-10-26 put midi sync debugging under a #def
2020-10-26 initialize MIDI early
    - otherwise, if configuring, then it gets missed as USB comes up
2020-10-26 update pending state when stopped
    - also fix silly bug in clock.h
2020-10-27 don't perplex on first sync ext clock
    when captureLastSample isn't valid, dNext won't be computed, and hence out of range
    but if the clock is running and things are sync, then this can because the user changed
    the settings - don't perplex in this case.
2020-10-27 improve compute order in isrClockCapture
    - qdiff can still be calculated if done before pending sequence or position changes
    - this lets the clock estimation still occur in these cases without skipping a ext. clock
    - position changing code is cleaned up a bit, removing some duplicate code
    - when changing the timing, let the isr handle updating the counts (if it is running)
2020-10-27 ignore (and flush) incoming MIDI when not MIDI sync'd
2020-10-28 add tiny font to display
2020-10-28 one more clock overhaul
    - make clockStopped a separate bool, not a ClockState
    - governs if clock advances with ext. clocks or not
    - otherwise, the clock estimation ignores it
    - reset clockStopped when changing sync modes
    - so a MIDI stop doesn't keep things from advancing when changing to another sync mode
    - rename forceTriggersOff to disableTriggers
2020-10-29 disable extended BPM option (force it on all the time)
2020-10-29 disable midi sync out
2020-10-30 v107b release
2021-06-19 fix sync to 1/4 bug
    also fixes unknown sync to DIN48 bug!
    also - totally embarrassing bug!!
2021-06-19 make ISR history circular
2021-06-19 get watchdog out of the way for now
2021-06-19 factor out ISR debug entry dump
2021-06-19 fix interrupt clearing
    this was the cause of the very occasional missed clock
2021-06-19 disable ISR debugging
2021-06-19 add VSC Arduino configuration and workspace files
    N.B.:
    - c_cpp_properties.json is ignored as the Arduino extension rebuilds it as needed
    - normal work flow will later arduino.json by adding details of your specific serial port in use - don't commit that change
2021-06-22 add readSequenceCount() to timer module
    this is faster than reading all the counts, if it is all we need
2021-06-26 provisional add of otherSync state
2021-06-26 generate interrupts from O pin
2021-06-26 correct upcomingClk calculation
2021-06-26 when setting other sync, reset clock stopped state appropriately
2021-06-26 alignment should only happen on O positive transitions
2021-06-26 osync isr debug
2021-06-26 nice UI field for Other Sync
2021-06-26 fixup: use graphic alignment UI for M & S
2021-06-27 implement next-memory function for other sync
2021-06-28 when switching other sync modes, ensure clock isn't stuck in stopped state
    also - if setting to one of the din/trigger sync modes, start/stop as appropriate
2021-06-28 bump version to 108 beta
2021-06-28 add images for v108 manual

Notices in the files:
parts and their libraries:
SparkFun-Jumpers: Licensing: Creative Commons ShareAlike 4.0 International - https://creativecommons.org/licenses/by-sa/4.0
